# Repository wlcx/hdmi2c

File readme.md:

# HDMI2C Monitor Controller

HDMI2C allows network control (via WiFi) of monitors connected to it via HDMI (via
[DDC]). This allows you to build your own tooling and control systems for your monitors,
rather than relying on awkward inconvient buttons and OSDs. Think of it as an API for
your monitors.

This repository contains the hardware design, made with [KiCAD]. You can see the
generated BOM and schematic [here][pages].

## What could you build with this

- A physical brightness knob
- Switch inputs of both monitors simultaneously when you wake up your desktop PC or
  connect your laptop to your dock
- IDK probably some other weird shit

## Features

- ESP32 WiFi MCU
- USB-C power and MCU serial connection
  - With blinkenlights
- Two HDMI ports with:
  - Level shifters to bring 5v DDC signals to 3.3v for the MCU.
  - 5v HDMI presence detection, switchable from the MCU. This allows us to fake being
    unplugged and replugged from HDMI, if we need to.
- Two forward facing buttons

## Firmware

It's floating around somewhere, I'll tidy it up and upload it at some point.

## A word on monitor compatibility

Not all monitors implement DDC that well. Particularly of annoyance, some models I
tested would not listen to DDC commands on inputs that were not active, which, given
this project relies on you having a spare HDMI input which never carries any video, is
kind of a deal breaker.

### Known good monitors

- Dell U2515h - I personally have two of these and they work flawlessly.

## Improvements for next rev

- Just use M3 mounting holes, M2.5 was a terrible idea
- Spare ESP32 IO broken out to headers for ease of hacking
- More ambitious, HDMI passthrough to allow use of the project without taking up a whole
  spare HDMI port.

## Is it that useful tho?

You can achieve the same thing without having to build your own hardware with a
Raspberry Pi 4. Support for dual monitor I2C (DDC) was added shortly before I started
this project - guess I didn't check enough :-). This is a much more accessible means to
achieve the same goal. However, if you want a more minimal solution that doesn't require
an entire embedded linux system, this project may be for you.

[DDC]: https://en.wikipedia.org/wiki/Display_Data_Channel
[KiCAD]: https://kicad.org
[pages]: https://wlcx.github.io/hdmi2c

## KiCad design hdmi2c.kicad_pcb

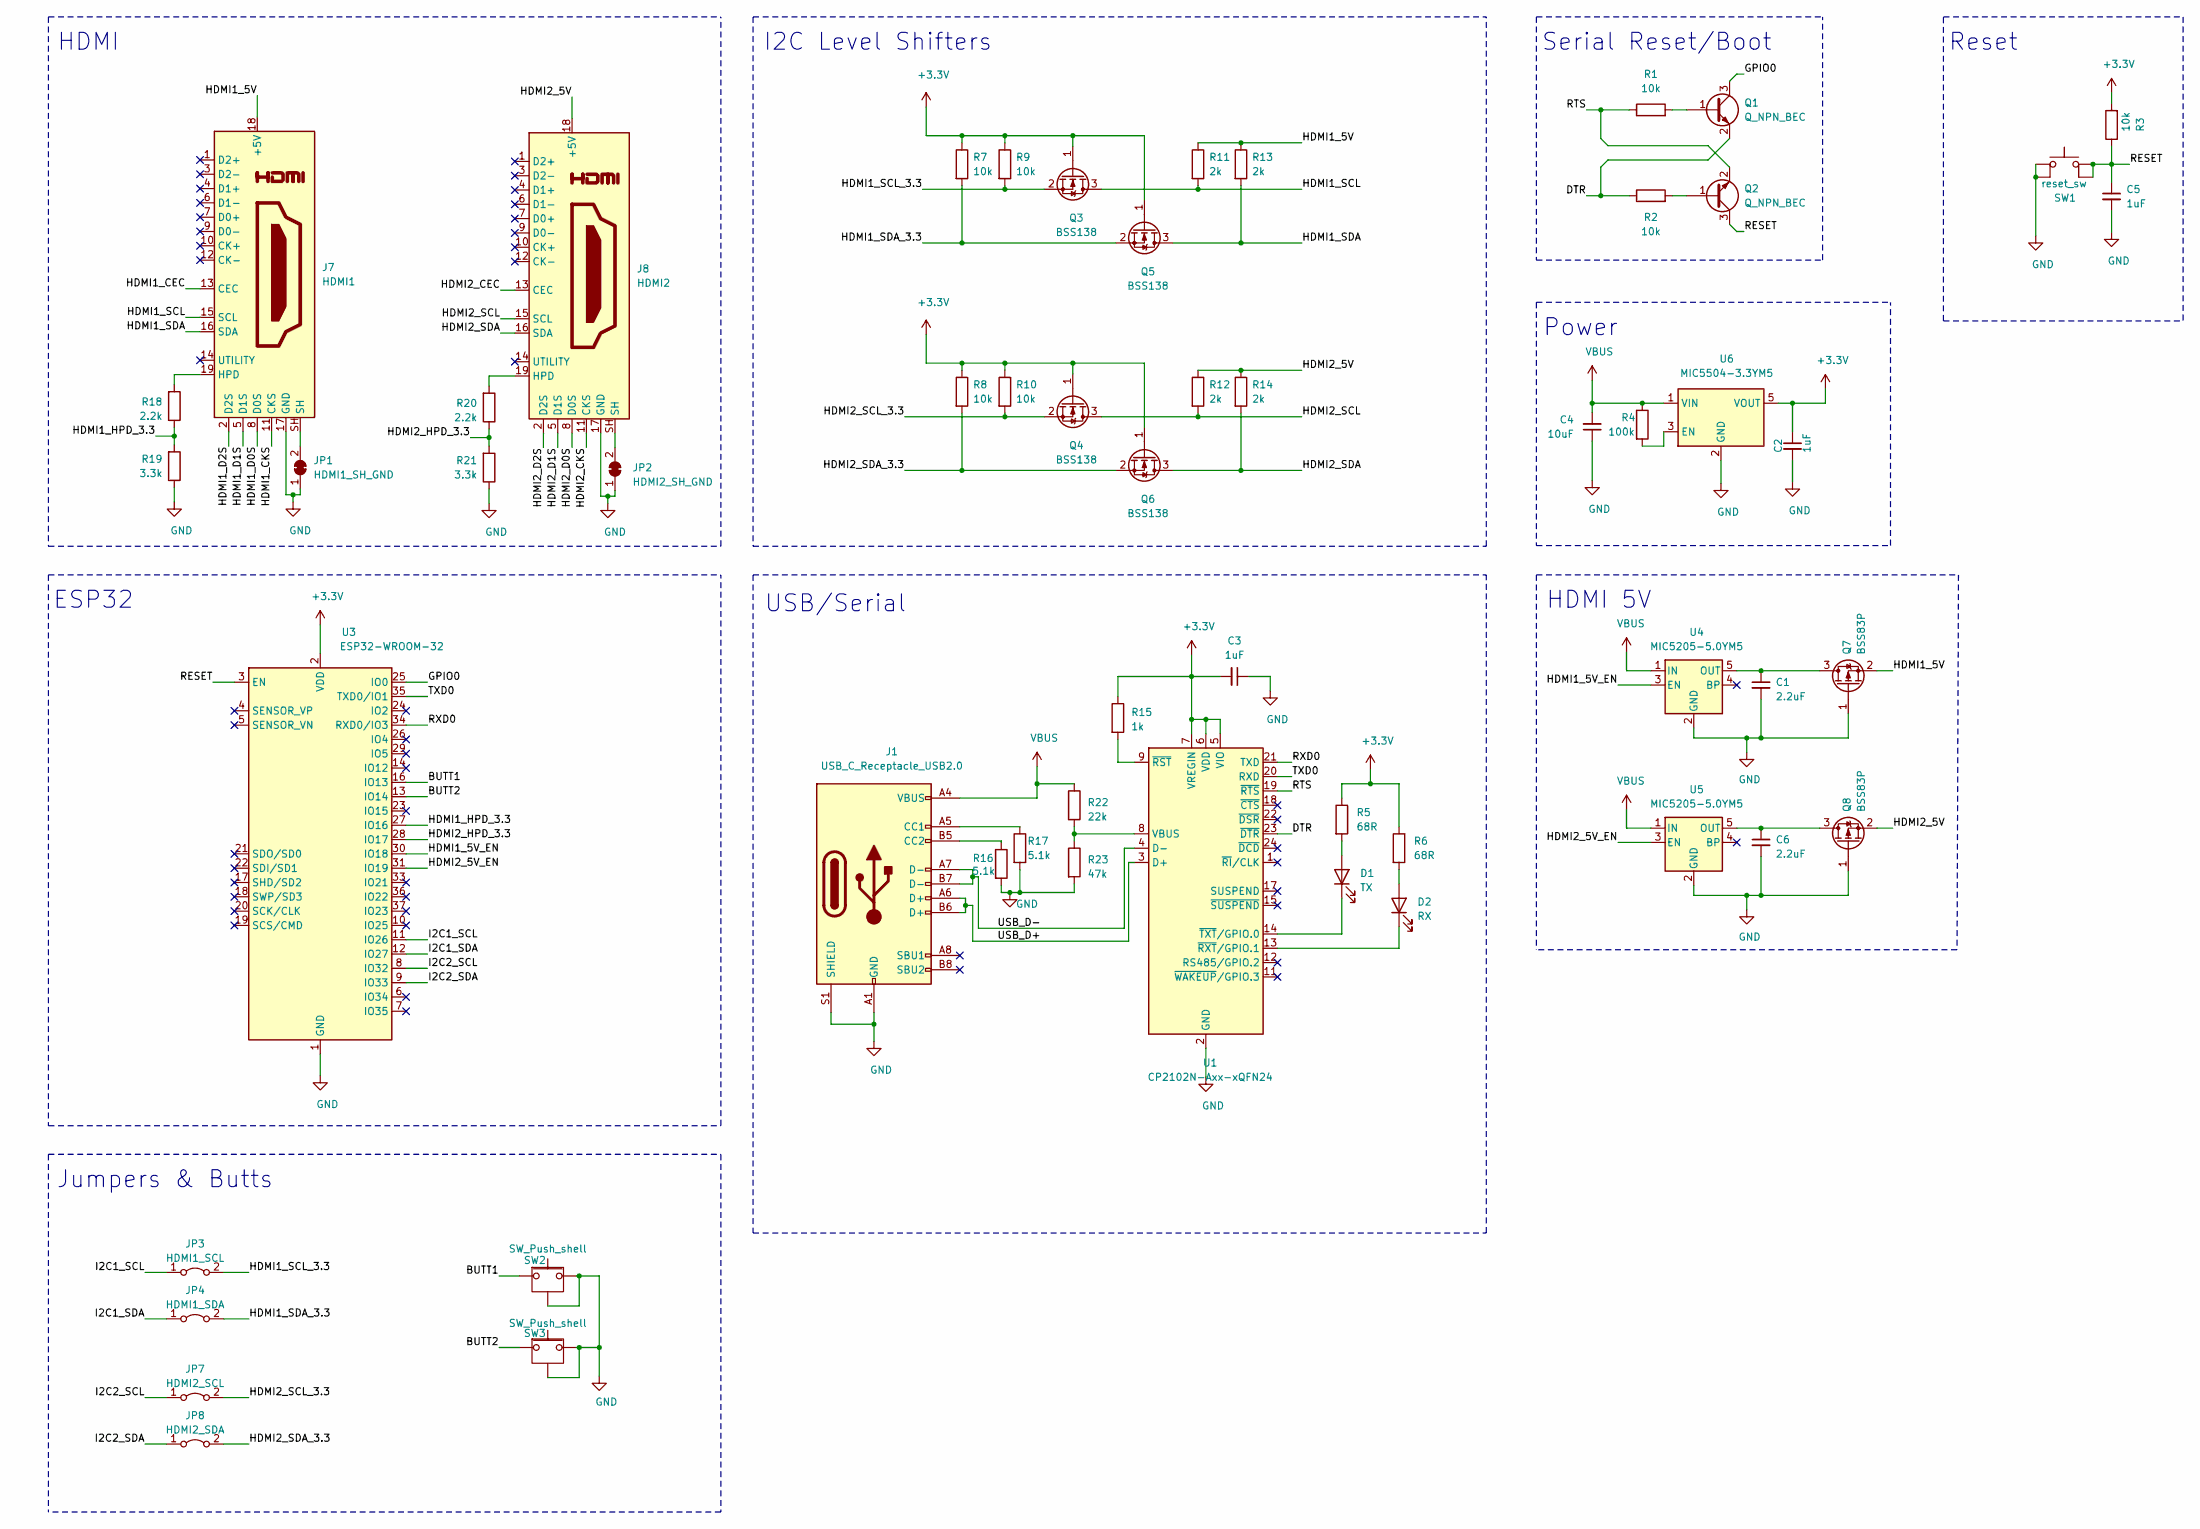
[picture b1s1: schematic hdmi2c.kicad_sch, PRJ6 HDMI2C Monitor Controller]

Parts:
C1, C6: 2.2uF; C_0603_1608Metric
C2, C3, C5: 1uF; C_0603_1608Metric
C4: 10uF; C_0603_1608Metric
D1: TX; LED_0603_1608Metric
D2: RX; LED_0603_1608Metric
J1: USB_C_Receptacle_USB2.0; USB_C_Receptacle_GCT_USB4085
J7: HDMI1; WURTH_685119134923_HDMI
J8: HDMI2; WURTH_685119134923_HDMI
JP1: HDMI1_SH_GND; SolderJumper-2_P1.3mm_Open_RoundedPad1.0x1.5mm
JP2: HDMI2_SH_GND; SolderJumper-2_P1.3mm_Open_RoundedPad1.0x1.5mm
JP3: HDMI1_SCL; SolderJumper-2_P1.3mm_Bridged_RoundedPad1.0x1.5mm
JP4: HDMI1_SDA; SolderJumper-2_P1.3mm_Bridged_RoundedPad1.0x1.5mm
JP7: HDMI2_SCL; SolderJumper-2_P1.3mm_Bridged_RoundedPad1.0x1.5mm
JP8: HDMI2_SDA; SolderJumper-2_P1.3mm_Bridged_RoundedPad1.0x1.5mm
Q1, Q2: Q_NPN_BEC; SOT-23
Q3, Q4, Q5, Q6: BSS138; SOT-23
Q7, Q8: BSS83P; SOT-23
R1, R2, R3, R7, R8, R9, R10: 10k; R_0603_1608Metric
R4: 100k; R_0603_1608Metric
R5, R6: 68R; R_0603_1608Metric
R11, R12, R13, R14: 2k; R_0603_1608Metric
R15: 1k; R_0603_1608Metric
R16, R17: 5.1k; R_0603_1608Metric
R18, R20: 2.2k; R_0603_1608Metric
R19, R21: 3.3k; R_0603_1608Metric
R22: 22k; R_0603_1608Metric
R23: 47k; R_0603_1608Metric
SW1: reset_sw; SW_SPST_Omron_B3FS-101xP
SW2, SW3: SW_Push_shell; SW_TH_Tactile_Omron_B3F-312x
U1: CP2102N-Axx-xQFN24; QFN-24-1EP_4x4mm_P0.5mm_EP2.6x2.6mm
U3: ESP32-WROOM-32
U4, U5: MIC5205-5.0YM5; SOT-23-5
U6: MIC5504-3.3YM5; SOT-23-5

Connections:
+3V3: C2.1, C3.2, Q3.1 (G), Q4.1 (G), Q5.1 (G), Q6.1 (G), R3.2, R5.1, R6.1, R7.1, R8.1, R9.1, R10.1, R15.1, U1.5 (VIO), U1.6 (VDD), U1.7 (VREGIN), U3.2 (VDD), U6.5 (VOUT)
/BUTT1: SW2.1, U3.16 (IO13)
/BUTT2: SW3.1, U3.13 (IO14)
/DTR: Q1.2 (E), R2.1, U1.23 (~DTR)
/GPIO0: Q1.3 (C), U3.25 (IO0)
/HDMI1_5V: J7.18 (+5V), Q7.2 (S), R11.1, R13.1
/HDMI1_5V_EN: U3.30 (IO18), U4.3 (EN)
/HDMI1_CEC: J7.13 (CEC)
/HDMI1_CKS: J7.11 (CKS)
/HDMI1_D0S: J7.8 (D0S)
/HDMI1_D1S: J7.5 (D1S)
/HDMI1_D2S: J7.2 (D2S)
/HDMI1_HPD_3.3: R18.1, R19.2, U3.27 (IO16)
/HDMI1_SCL: J7.15 (SCL), Q3.3 (D), R11.2
/HDMI1_SCL_3.3: JP3.2 (B), Q3.2 (S), R9.2
/HDMI1_SDA: J7.16 (SDA), Q5.3 (D), R13.2
/HDMI1_SDA_3.3: JP4.2 (B), Q5.2 (S), R7.2
/HDMI2_5V: J8.18 (+5V), Q8.2 (S), R12.1, R14.1
/HDMI2_5V_EN: U3.31 (IO19), U5.3 (EN)
/HDMI2_CEC: J8.13 (CEC)
/HDMI2_CKS: J8.11 (CKS)
/HDMI2_D0S: J8.8 (D0S)
/HDMI2_D1S: J8.5 (D1S)
/HDMI2_D2S: J8.2 (D2S)
/HDMI2_HPD_3.3: R20.1, R21.2, U3.28 (IO17)
/HDMI2_SCL: J8.15 (SCL), Q4.3 (D), R12.2
/HDMI2_SCL_3.3: JP7.2 (B), Q4.2 (S), R10.2
/HDMI2_SDA: J8.16 (SDA), Q6.3 (D), R14.2
/HDMI2_SDA_3.3: JP8.2 (B), Q6.2 (S), R8.2
/I2C1_SCL: JP3.1 (A), U3.11 (IO26)
/I2C1_SDA: JP4.1 (A), U3.12 (IO27)
/I2C2_SCL: JP7.1 (A), U3.8 (IO32)
/I2C2_SDA: JP8.1 (A), U3.9 (IO33)
/RESET: C5.1, Q2.3 (C), R3.1, SW1.3, SW1.4, U3.3 (EN)
/RTS: Q2.2 (E), R1.1, U1.19 (~RTS)
/RXD0: U1.21 (TXD), U3.34 (RXD0/IO3)
/TXD0: U1.20 (RXD), U3.35 (TXD0/IO1)
/USB_D+: J1.A6 (D+), J1.B6 (D+), U1.3 (D+)
/USB_D-: J1.A7 (D-), J1.B7 (D-), U1.4 (D-)
GND: C1.2, C2.2, C3.1, C4.1, C5.2, C6.2, J1.A1 (GND), J1.A12 (GND), J1.B1 (GND), J1.B12 (GND), J1.S1 (SHIELD), J7.17 (GND), J8.17 (GND), JP1.1 (A), JP2.1 (A), Q7.1 (G), Q8.1 (G), R16.2, R17.2, R19.1, R21.1, R23.2, SW1.1, SW1.2, SW2.2, SW2.SH (Shell), SW3.2, SW3.SH (Shell), U1.2 (GND), U1.25 (GND), U3.1 (GND), U3.15 (GND), U3.38 (GND), U3.39 (GND), U4.2 (GND), U5.2 (GND), U6.2 (GND)
unnamed: C1.1, Q7.3 (D), U4.5 (OUT)
unnamed: C6.1, Q8.3 (D), U5.5 (OUT)
unnamed: D1.1 (K), U1.14 (~TXT~/GPIO.0)
unnamed: D1.2 (A), R5.2
unnamed: D2.1 (K), U1.13 (~RXT~/GPIO.1)
unnamed: D2.2 (A), R6.2
unnamed: J1.A5 (CC1), R17.1
unnamed: J1.B5 (CC2), R16.1
unnamed: J7.19 (HPD), R18.2
unnamed: J7.SH, JP1.2 (B)
unnamed: J8.19 (HPD), R20.2
unnamed: J8.SH, JP2.2 (B)
unnamed: Q1.1 (B), R1.2
unnamed: Q2.1 (B), R2.2
unnamed: R4.2, U6.3 (EN)
unnamed: R15.2, U1.9 (~RST)
unnamed: R22.2, R23.1, U1.8 (VBUS)
VBUS: C4.2, J1.A4 (VBUS), J1.A9 (VBUS), J1.B4 (VBUS), J1.B9 (VBUS), R4.1, R22.1, U4.1 (IN), U5.1 (IN), U6.1 (VIN)

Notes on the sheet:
I2C Level Shifters
Reset
HDMI 5V
Power
Serial Reset/Boot
HDMI
USB/Serial
Jumpers & Butts
ESP32

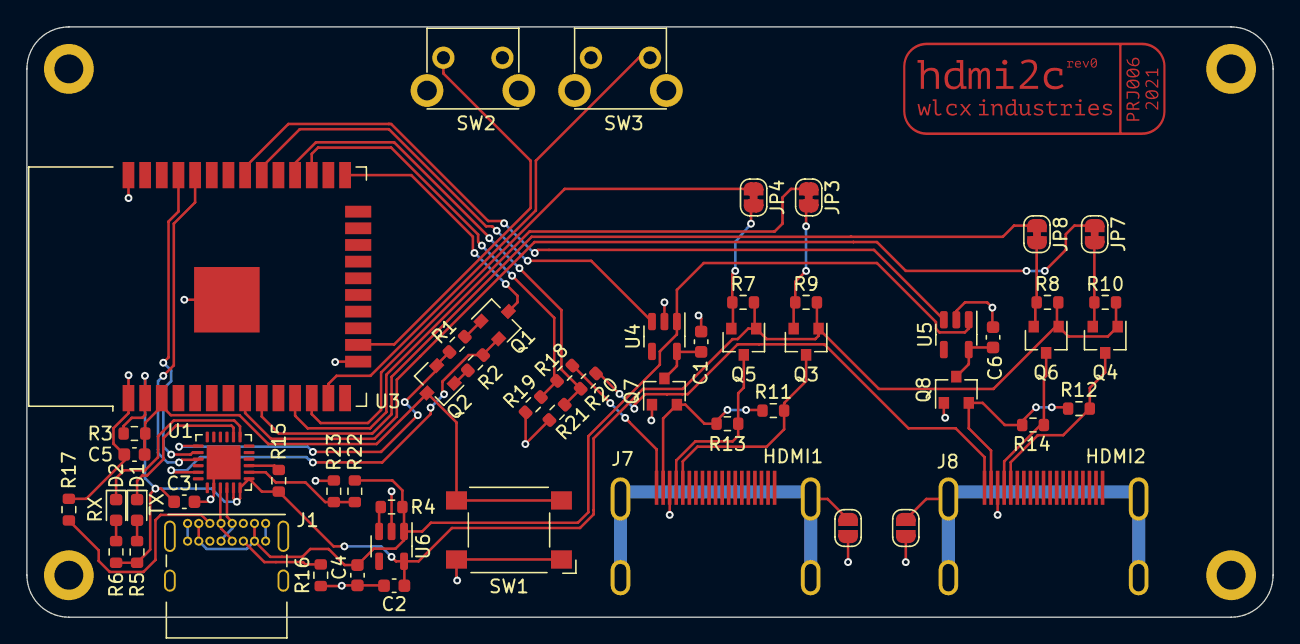
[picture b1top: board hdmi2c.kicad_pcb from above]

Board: 2 copper layers, 95.0 x 45.0 mm, 61 parts (0 on the bottom side), 48 nets.

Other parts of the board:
M1, M2, M3, M4: MountingHole_2.2mm_M2_DIN965_Pad_with_paste
svg2mod: G***; logo

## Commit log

2021-06-25 Rev 0
2021-06-25 Add interactive BOM gh action
2021-06-25 Update PCB sheet properties
2022-08-09 Save project files with newest kicad version
2022-08-09 Update schematic/pcb metadata to match
2022-08-10 Deploy static site to github pages
2022-08-11 Add readme
